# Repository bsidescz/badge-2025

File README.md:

# badge-2025
Repo containing all the badge bits and pieces

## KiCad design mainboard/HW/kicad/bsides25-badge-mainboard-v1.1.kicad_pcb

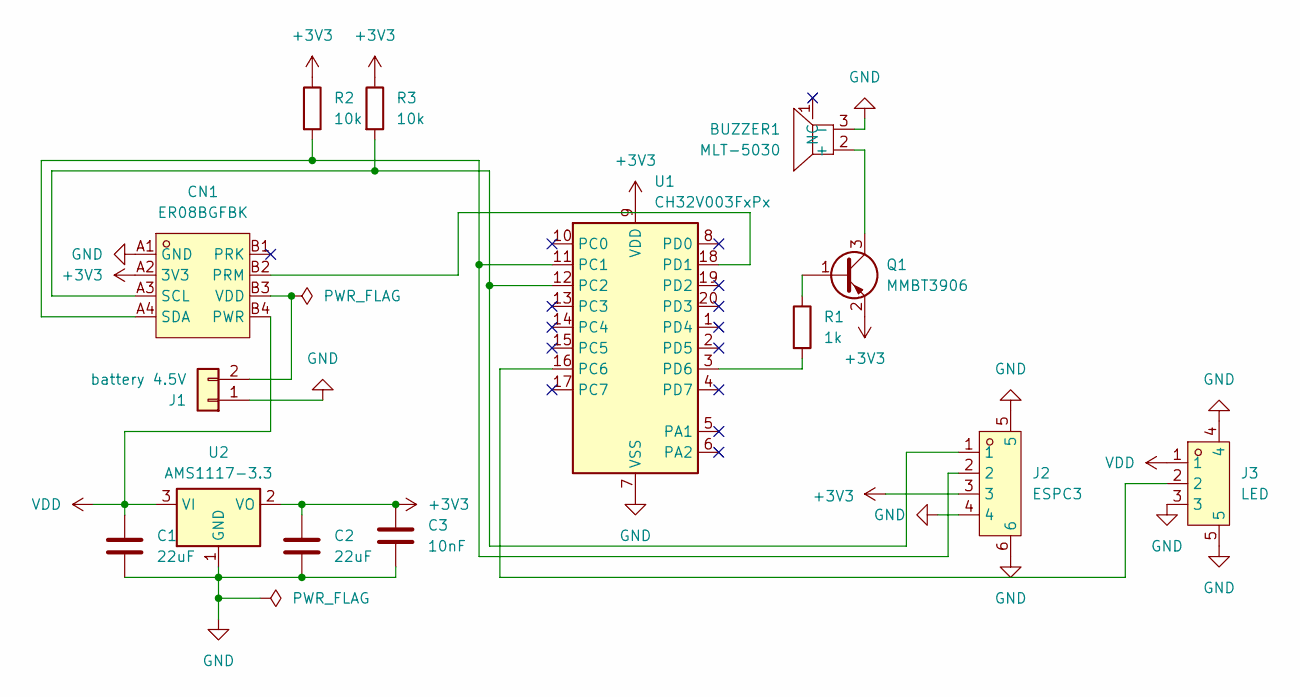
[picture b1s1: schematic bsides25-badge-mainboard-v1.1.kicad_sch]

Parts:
BUZZER1: MLT-5030; BUZ-SMD_3P-L5.2-W5.2-P3.50-BR; LCSC Part C95297
C1, C2: 22uF; C_0603_1608Metric
C3: 10nF; C_0603_1608Metric
CN1: ER08BGFBK; CONN-TH_ER08BGFBK; LCSC Part C5173326
J1: battery 4.5V; SolderWire-0.1sqmm_1x02_P3.6mm_D0.4mm_OD1mm
J2: ESPC3; CONN-SMD_4P-P1.00_WAFER-SH1.0-4PWB; LCSC Part C3029343
J3: LED; CONN-SMD_3P-P1.00_WAFER-SH1.0-3PWB; LCSC Part C3029342
Q1: MMBT3906; SOT-23
R1: 1k; R0603
R2, R3: 10k; R0603
U1: CH32V003FxPx; TSSOP-20_4.4x6.5mm_P0.65mm
U2: AMS1117-3.3; SOT-223-3_TabPin2

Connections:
+3V3: C2.1, C3.1, CN1.A2 (3V3), J2.3, Q1.2 (E), R2.1, R3.1, U1.9 (VDD), U2.2 (VO)
GND: BUZZER1.3 (-), C1.2, C2.2, C3.2, CN1.A1 (GND), J1.1, J2.4, J2.5, J2.6, J3.3, J3.4, J3.5, U1.7 (VSS), U2.1 (GND)
unnamed: BUZZER1.2 (+), Q1.3 (C)
unnamed: CN1.B2 (PRM), U1.18 (PD1)
unnamed: CN1.A3 (SCL), J2.1, R3.2, U1.12 (PC2)
unnamed: CN1.A4 (SDA), J2.2, R2.2, U1.11 (PC1)
unnamed: CN1.B3 (VDD), J1.2
unnamed: Q1.1 (B), R1.1
unnamed: J3.2, U1.16 (PC6)
unnamed: R1.2, U1.3 (PD6)
VDD: C1.1, CN1.B4 (PWR), J3.1, U2.3 (VI)

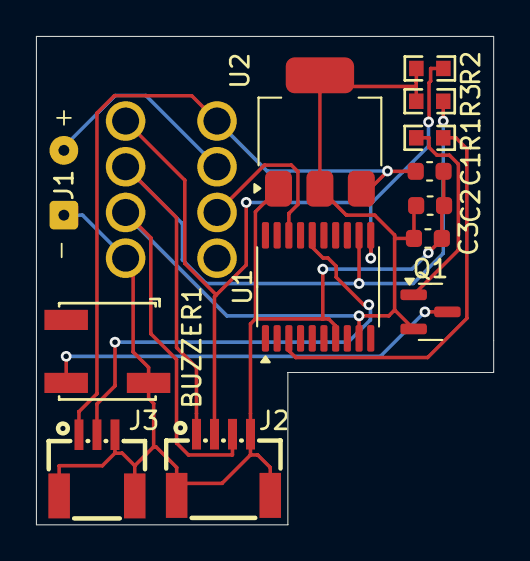
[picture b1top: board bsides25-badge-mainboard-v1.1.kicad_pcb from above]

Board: 2 copper layers, 25.4 x 27.1 mm, 14 parts (1 on the bottom side), 11 nets.

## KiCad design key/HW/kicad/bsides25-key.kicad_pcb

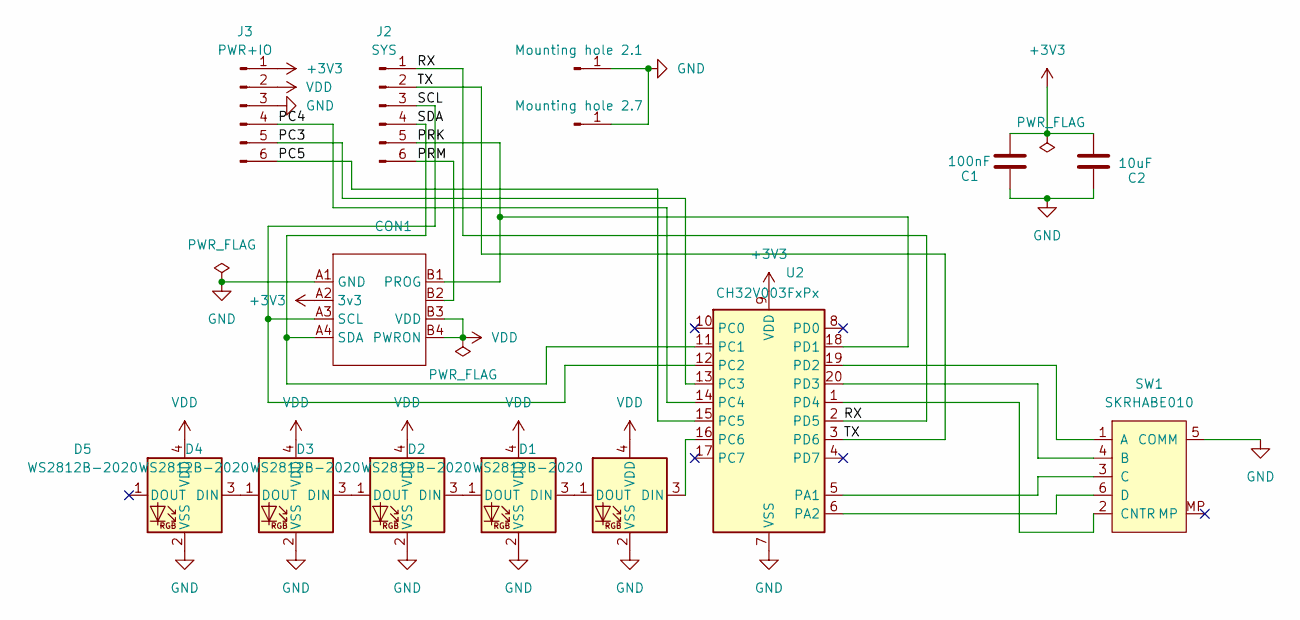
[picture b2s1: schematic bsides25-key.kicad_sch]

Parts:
C1: 100nF; C_0201_0603Metric_Pad0.64x0.40mm_HandSolder
C2: 10uF; C_0201_0603Metric_Pad0.64x0.40mm_HandSolder
CON1: EDGE_BADGE
D1, D2, D3, D4, D5: WS2812B-2020; LED_WS2812B-2020_PLCC4_2.0x2.0mm
J1: Mounting hole 2.1; MountingHole_2.1mm
J2: SYS; PinHeader_1x06_P2.54mm_Vertical
J3: PWR+IO; PinHeader_1x06_P2.54mm_Vertical
J4: Mounting hole 2.7; MountingHole_2.7mm
SW1: SW_SKRHABE010_SMD; MPN SKRHABE010
U2: CH32V003FxPx; TSSOP-20_4.4x6.5mm_P0.65mm

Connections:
+3V3: C1.1, C2.1, CON1.A2 (3v3), J3.1, U2.9 (VDD)
/PC3: J3.5, U2.13 (PC3)
/PC4: J3.4, U2.14 (PC4)
/PC5: J3.6, U2.15 (PC5)
/PRK: CON1.B1 (PROG), J2.5, U2.18 (PD1)
/PRM: CON1.B2, J2.6
/RX: J2.1, U2.2 (PD5)
/SCL: CON1.A3 (SCL), J2.3, U2.12 (PC2)
/SDA: CON1.A4 (SDA), J2.4, U2.11 (PC1)
/TX: J2.2, U2.3 (PD6)
GND: C1.2, C2.2, CON1.A1 (GND), D1.2 (VSS), D2.2 (VSS), D3.2 (VSS), D4.2 (VSS), D5.2 (VSS), J1.1, J3.3, J4.1, SW1.5 (COMM), U2.7 (VSS)
unnamed: D1.3 (DIN), U2.16 (PC6)
unnamed: D1.1 (DOUT), D2.3 (DIN)
unnamed: D2.1 (DOUT), D3.3 (DIN)
unnamed: D3.1 (DOUT), D4.3 (DIN)
unnamed: D4.1 (DOUT), D5.3 (DIN)
unnamed: SW1.1 (A), U2.19 (PD2)
unnamed: SW1.4 (B), U2.20 (PD3)
unnamed: SW1.3 (C), U2.5 (PA1)
unnamed: SW1.2 (CNTR), U2.1 (PD4)
unnamed: SW1.6 (D), U2.6 (PA2)
VDD: CON1.B3 (VDD), CON1.B4 (PWRON), D1.4 (VDD), D2.4 (VDD), D3.4 (VDD), D4.4 (VDD), D5.4 (VDD), J3.2

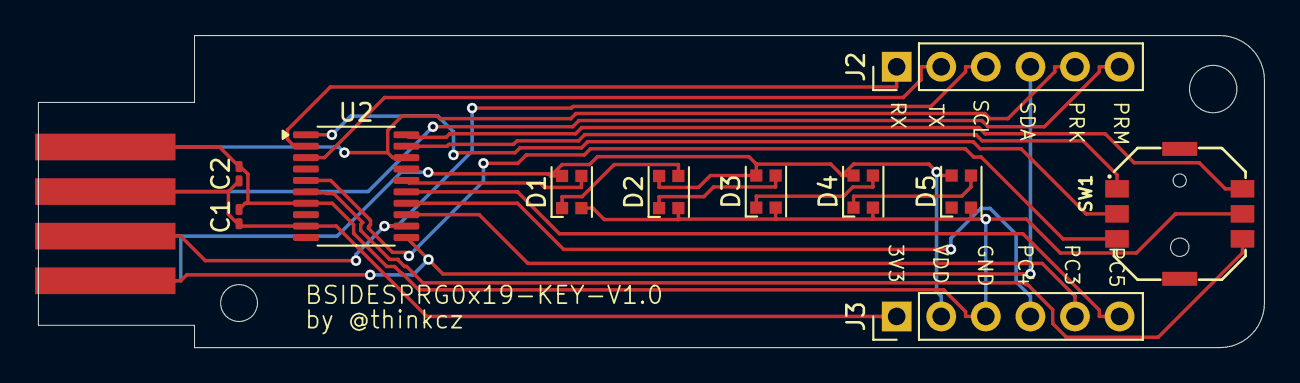
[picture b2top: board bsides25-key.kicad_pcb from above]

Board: 2 copper layers, 69.9 x 17.8 mm, 14 parts (0 on the bottom side), 22 nets.

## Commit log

2025-04-08 founding commit of BSides Badge 2025
2025-09-16 key cover for 3D printing

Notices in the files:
parts and their libraries:
License: Apache-2.0
